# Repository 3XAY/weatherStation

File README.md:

# weatherStation

A submission for a ysws called Asylum by Hack Club.
This weather station gets the weather data from online.
It also can check if your server(s) are up.
Finally, it has a mmWave presence detection sensor to automatically turn lights on/off in your room with Google Home.
Note that this has custom hardware, but only works on the Sprig as of now, due to shipping times.
[Demo video/site](https://3xay.github.io/Projects/HackClub/asylum-weather)

All of the code is in Circuitpython

### BOM:
- Wemos ESP32-C3 Mini
- ST7735 128x160 SPI TFT Display
- EC11 Encoder with switch
- Seeed mmWave Human Presence Detection Sensor (101991030)
- 1x 10Ohm THT Resistor
- PCB
- 3D Printed Case

## Schematic:

## PCB:

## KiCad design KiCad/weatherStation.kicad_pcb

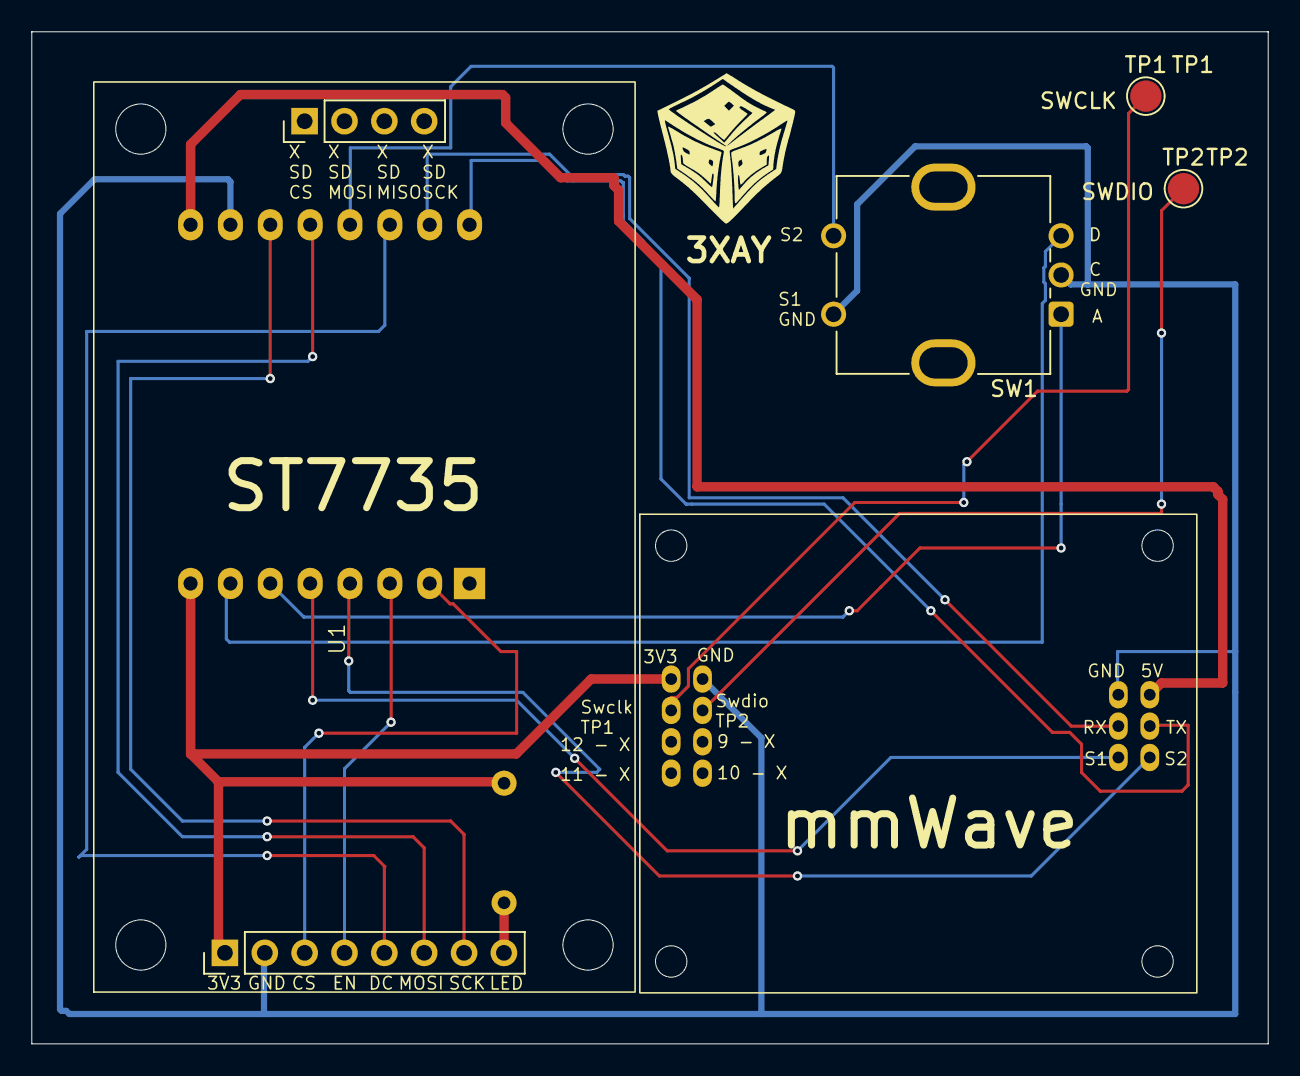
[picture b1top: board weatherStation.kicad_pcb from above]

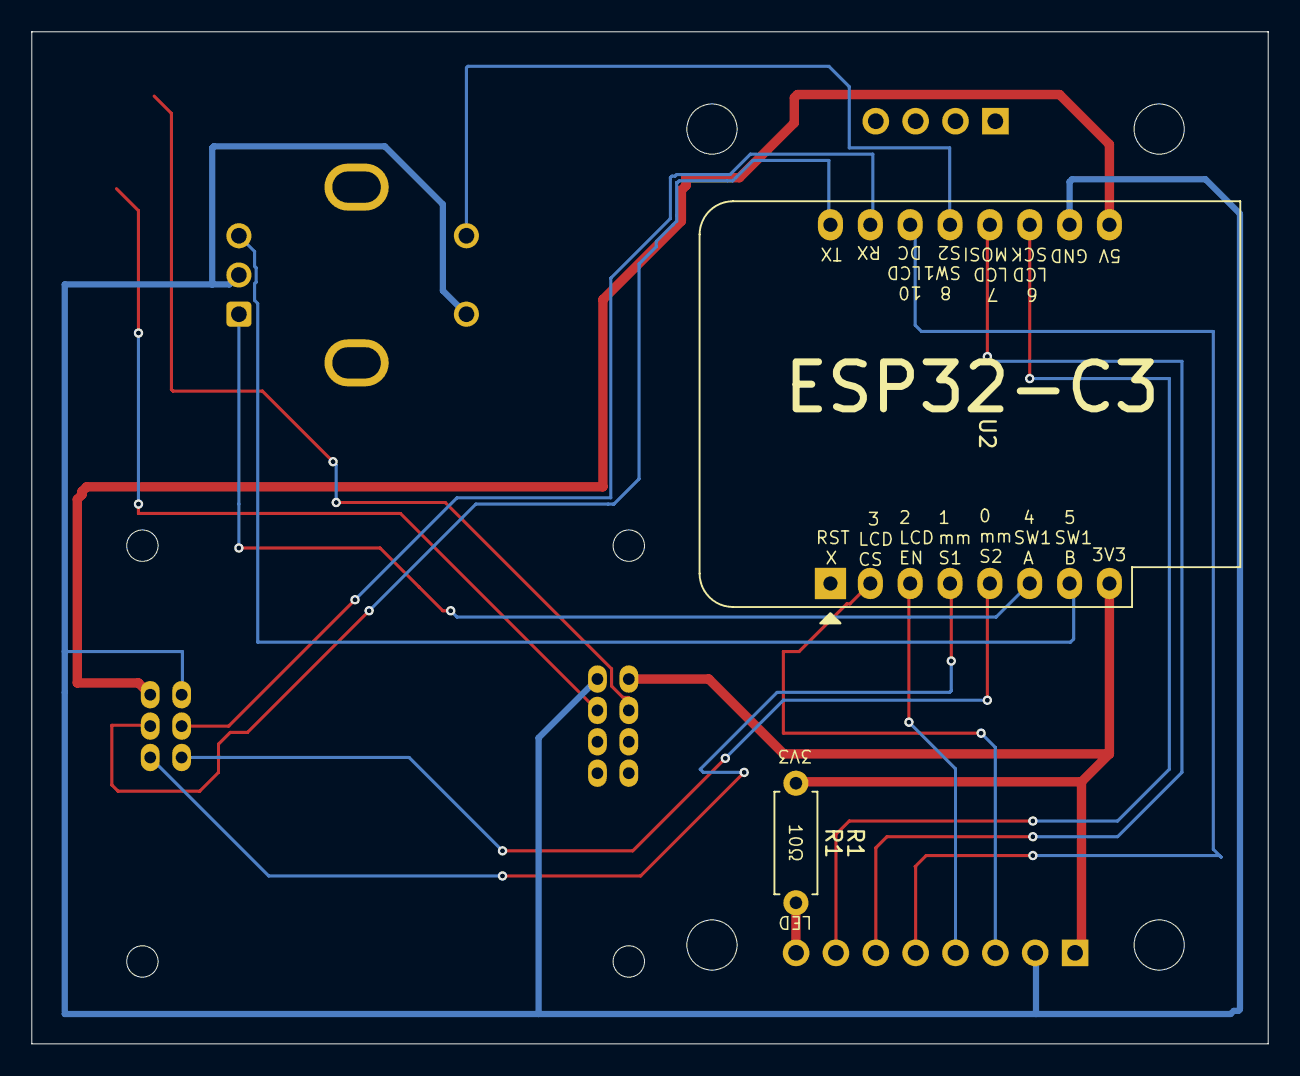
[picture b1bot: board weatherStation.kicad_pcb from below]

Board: 2 copper layers, 78.8 x 64.5 mm, 7 parts (2 on the bottom side), 18 nets.

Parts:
R1: R; R_Axial_DIN0207_L6.3mm_D2.5mm_P7.62mm_Horizontal
SW1: RotaryEncoder_Switch; RotaryEncoder_Bourns_Vertical_PEC12R-3x17F-Sxxxx
TP1, TP2: TestPoint; TestPoint_Pad_D2.0mm
U1: TFT_ST7735_SD
U2: WEMOS_C3_Mini; WEMOS_D1_mini_light
U3: Untitled_1

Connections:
+3V3: R1.1, U1.1 (3V3), U2.8 (3V3), U3.11 (3V3)
+5V: U2.9 (5V), U3.1 (5V)
FWDebug: TP1.1, U3.12 (Swclk)
FWDebug2: TP2.1, U3.8 (Swdio)
GND: SW1.C, SW1.S1, U1.2 (GND), U2.10 (GND), U3.4 (GND), U3.7 (GND)
unnamed: U1.5 (D/C), U2.14 (CS0/IO10)
unnamed: U1.4 (EN), U2.3 (MISO/IO2)
unnamed: U1.3 (LCD_CS), U2.2 (IO3)
unnamed: U1.6 (LCD_MOSI), U2.12 (MOSI/IO7)
unnamed: U1.7 (LCD_SCK), U2.11 (SCK/IO6)
unnamed: R1.2, U1.8 (LED)
unnamed: SW1.A, U2.6 (IO4)
unnamed: SW1.B, U2.7 (IO5)
unnamed: SW1.S2, U2.13 (IO8)
unnamed: U2.15 (RX), U3.5 (Tx)
unnamed: U2.16 (TX), U3.2 (Rx)
mmS1: U2.4 (IO1), U3.3 (S1)
mmS2: U2.5 (IO0), U3.6 (S2)

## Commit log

2024-12-13 Upload files
    I forgot to make a repo for this project, whoops!
2024-12-13 Fixed minor PCB errors
    Fixed errors introduced after migrating to this repo
    Fixed mmWave footprint having silkscreen on hole
2024-12-13 Case V1 + Minor KiCad
    Tried to export PCB from KiCad to Blender, need KiCad 8, not 8.99.
    Made a basic case that using the unused mounting points from the PCB to hang the PCB. Must be at a 90 degree angle for mmWave sensor.
2024-12-14 Case V1 Review
2024-12-14 Create test code on Sprig, displays button "W" state. Can be modified to make weather station code
2024-12-15 - Remove button press tester and add weather data - Remove example code from internet - Add template for settings.toml
2024-12-15 More code (I forgot what I did)
2024-12-20 Add images
2024-12-20 Add libs to firmware folder, made wifi connect after setting up display, fixed wifi connction
2024-12-20 Fix images overlapping text Attempt to get KiCad wakatime extension working Added connecting to wifi text Added some comments
2024-12-20 Fix memory leak Add tabs.md
2024-12-20 Fix tabs.md to be in list form
2024-12-20 Update readme Add screenshots
2025-01-28 Rename weatherStation.kicad_pcb to weatherStation.kicad_pcb
